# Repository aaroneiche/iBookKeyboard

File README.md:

# iBook Keyboard & Trackpad adapter

This board is a controller to drive a keyboard and trackpad on an Apple Clamshell iBook G3 - the original iBooks.

### Huh?

Yeah, I'm in the process of making an iBook chassis into a modern computer, and this is the first step. You can find more information (and progress) on this project at the [project page on my website](https://aaroneiche.com/projects/pibook).

### What are the JST connectors for?
Eventually I hope to integrate the controls for the Power button, trackpad button, and the lid-closed sensor (a magnetic *reed switch*). I haven't gotten to that yet, so for right now, they're just connectors that go to GPIO on the RP2040.

The RGB out is something where I'm hoping to support RGB LEDs to pass through the keyboard for fun. This is a "bells and whistles" type thing, and might not ever get addressed.

### Can I use it?
Yes, you can. But please be aware that I haven't finalized the design and I'm not sure that it'll work 100% yet. Also, the firmware is in an incomplete state (and not included in this repo yet), so *caveat emptor*. That said, if you have questions feel free to send me a message. I'm happy to help where I can.

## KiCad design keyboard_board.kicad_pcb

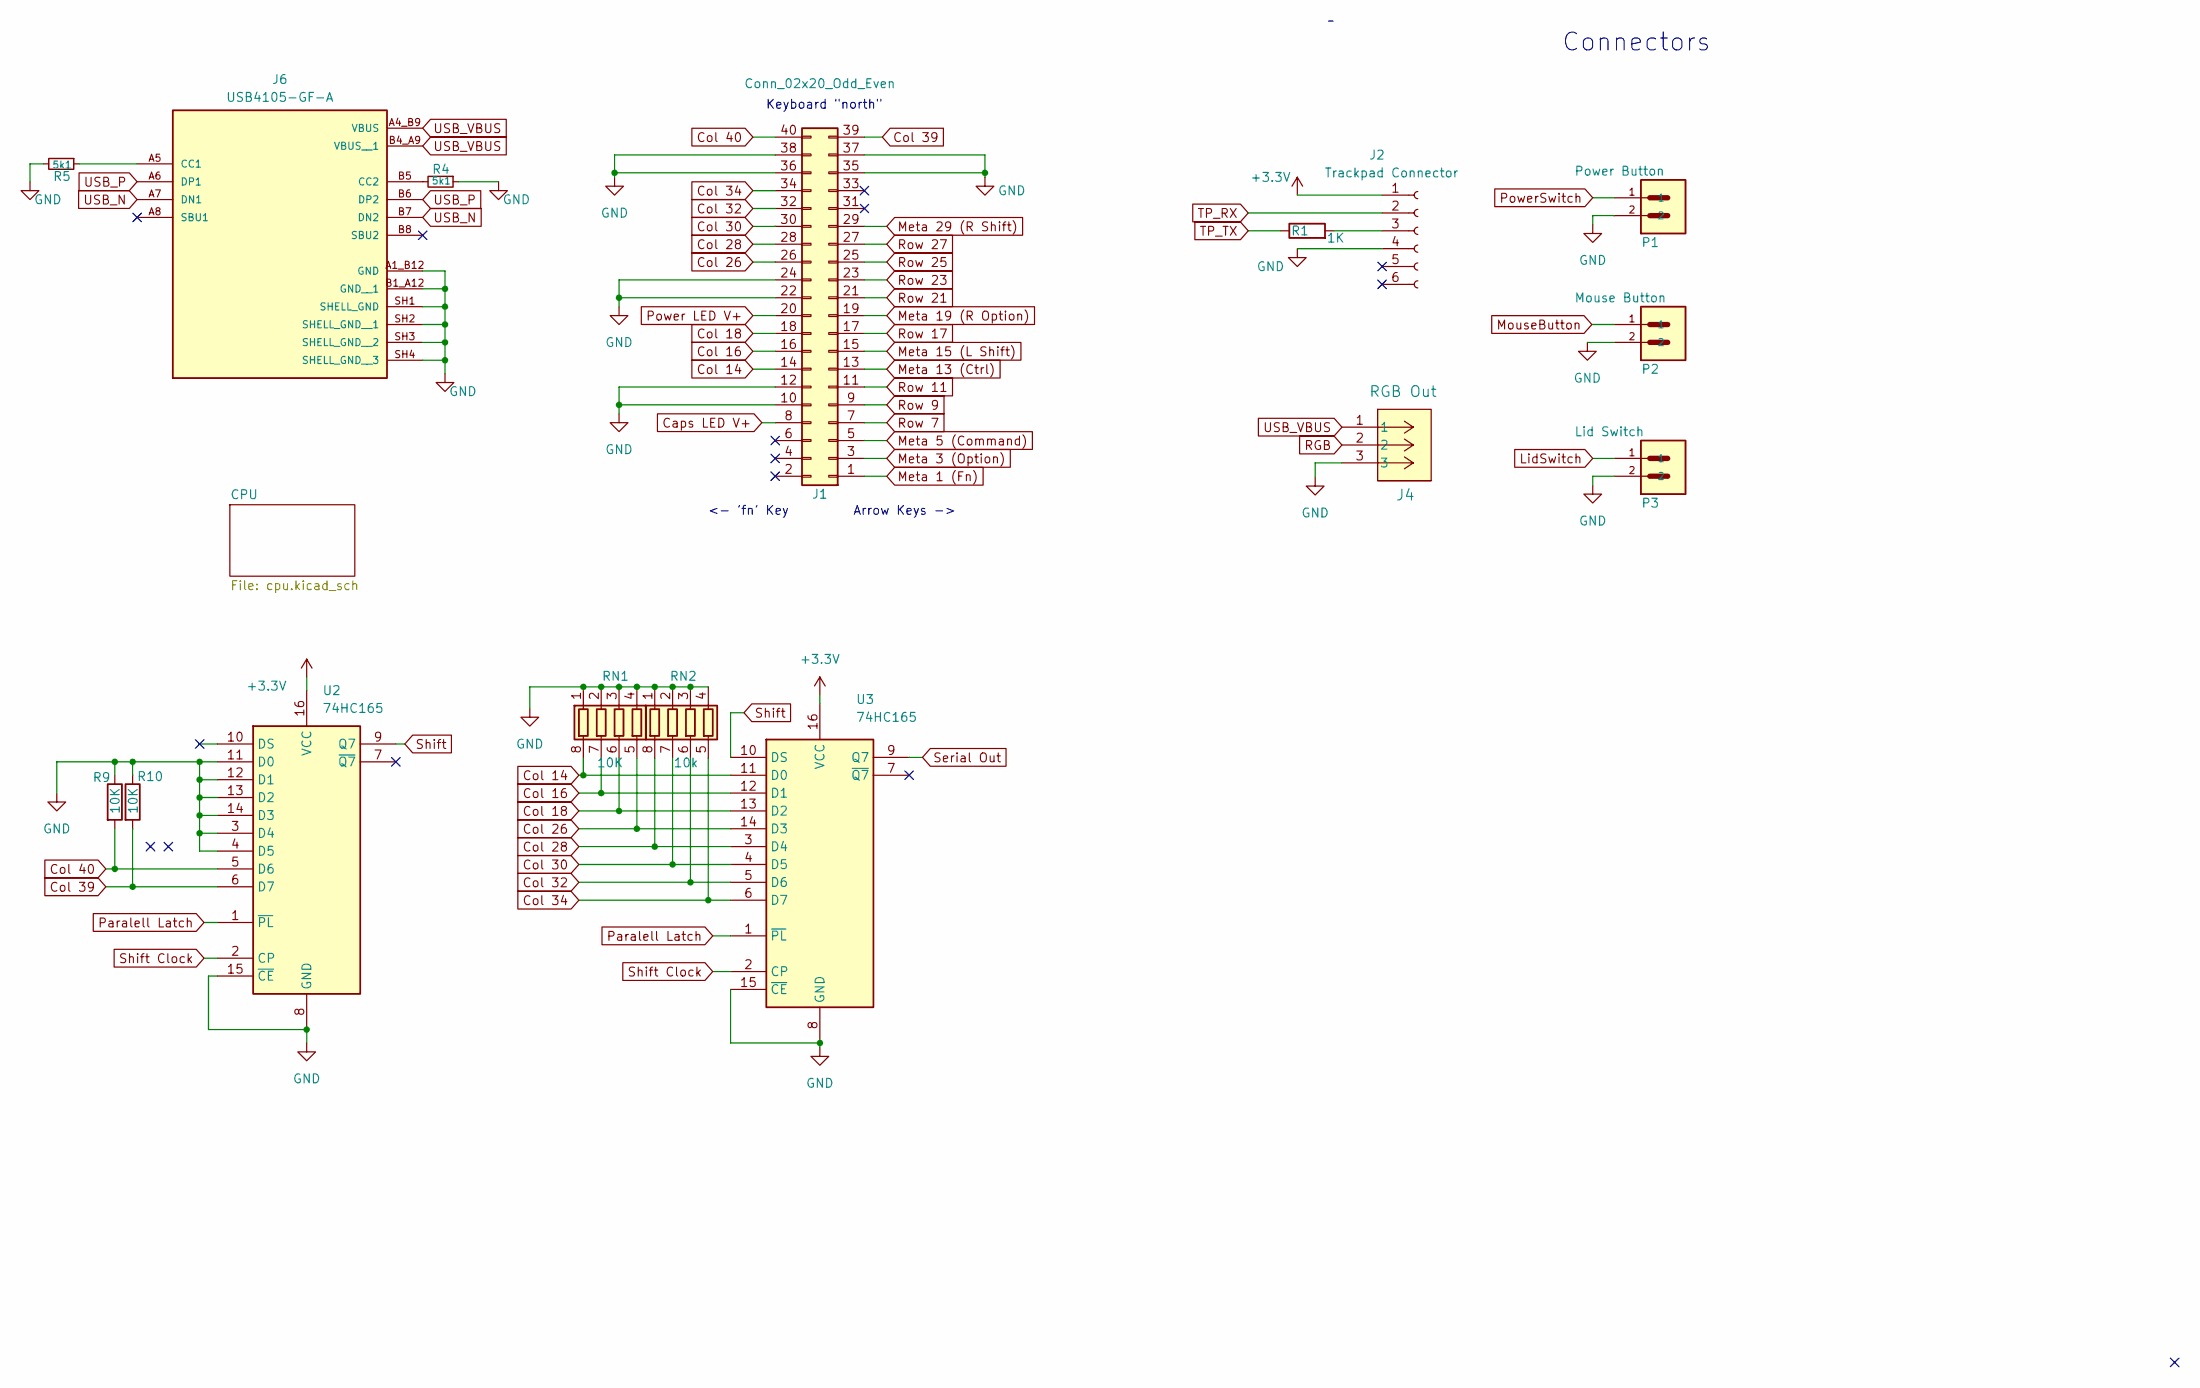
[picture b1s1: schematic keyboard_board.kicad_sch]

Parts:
J1: Conn_02x20_Odd_Even; 2x20_1.27_DIP_F
J2: Trackpad Connector; AMPHENOL_SFW6S-2STE1LF
J4: RGB Out; CONN3_S3B-PH_JST
J6: USB4105-GF-A; GCT_USB4105-GF-A; PARTREV B4
P1: Power Button; JST_S2B-PH-SM4-TB
P2: Mouse Button; JST_S2B-PH-SM4-TB
P3: Lid Switch; JST_S2B-PH-SM4-TB
R1: 1K; R_0805_2012Metric
R4, R5: 5k1; R_0603_1608Metric
R9, R10: 10K; R_0805_2012Metric
RN1: 10K; R_Array_Convex_4x1206
RN2: 10k; R_Array_Convex_4x1206
U2, U3: 74HC165; D16-L

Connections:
+3.3V: J2.1, U2.16 (VCC), U3.16 (VCC); also elsewhere on the board
Caps LED V+: J1.8; also elsewhere on the board
Col 14: J1.14, RN1.8 (R1.2), U3.11 (D0)
Col 16: J1.16, RN1.7 (R2.2), U3.12 (D1)
Col 18: J1.18, RN1.6 (R3.2), U3.13 (D2)
Col 26: J1.26, RN1.5 (R4.2), U3.14 (D3)
Col 28: J1.28, RN2.8 (R1.2), U3.3 (D4)
Col 30: J1.30, RN2.7 (R2.2), U3.4 (D5)
Col 32: J1.32, RN2.6 (R3.2), U3.5 (D6)
Col 34: J1.34, RN2.5 (R4.2), U3.6 (D7)
Col 39: J1.39, R10.2, U2.6 (D7)
Col 40: J1.40, R9.2, U2.5 (D6)
GND: J1.10, J1.12, J1.22, J1.24, J1.35, J1.36, J1.37, J1.38, J2.4, J4.3, J6.A1_B12 (GND), J6.B1_A12 (GND__1), J6.SH1 (SHELL_GND), J6.SH2 (SHELL_GND__1), J6.SH3 (SHELL_GND__2), J6.SH4 (SHELL_GND__3), P1.2, P2.2, P3.2, R4.1, R5.2, R9.1, R10.1, RN1.1 (R1.1), RN1.2 (R2.1), RN1.3 (R3.1), RN1.4 (R4.1), RN2.1 (R1.1), RN2.2 (R2.1), RN2.3 (R3.1), RN2.4 (R4.1), U2.3 (D4), U2.4 (D5), U2.8 (GND), U2.11 (D0), U2.12 (D1), U2.13 (D2), U2.14 (D3), U2.15 (~CE), U3.8 (GND), U3.15 (~CE); also elsewhere on the board
LidSwitch: P3.1; also elsewhere on the board
Meta 1 (Fn): J1.1; also elsewhere on the board
Meta 3 (Option): J1.3; also elsewhere on the board
Meta 5 (Command): J1.5; also elsewhere on the board
Meta 13 (Ctrl): J1.13; also elsewhere on the board
Meta 15 (L Shift): J1.15; also elsewhere on the board
Meta 19 (R Option): J1.19; also elsewhere on the board
Meta 29 (R Shift): J1.29; also elsewhere on the board
MouseButton: P2.1; also elsewhere on the board
unnamed: J2.3, R1.2
unnamed: J6.A5 (CC1), R5.1
unnamed: J6.B5 (CC2), R4.2
Paralell Latch: U2.1 (~PL), U3.1 (~PL); also elsewhere on the board
Power LED V+: J1.20; also elsewhere on the board
PowerSwitch: P1.1; also elsewhere on the board
RGB: J4.2; also elsewhere on the board
Row 7: J1.7; also elsewhere on the board
Row 9: J1.9; also elsewhere on the board
Row 11: J1.11; also elsewhere on the board
Row 17: J1.17; also elsewhere on the board
Row 21: J1.21; also elsewhere on the board
Row 23: J1.23; also elsewhere on the board
Row 25: J1.25; also elsewhere on the board
Row 27: J1.27; also elsewhere on the board
Serial Out: U3.9 (Q7); also elsewhere on the board
Shift: U2.9 (Q7), U3.10 (DS)
Shift Clock: U2.2 (CP), U3.2 (CP); also elsewhere on the board
TP_RX: J2.2; also elsewhere on the board
TP_TX: R1.1; also elsewhere on the board
USB_N: J6.A7 (DN1), J6.B7 (DN2); also elsewhere on the board
USB_P: J6.A6 (DP1), J6.B6 (DP2); also elsewhere on the board
USB_VBUS: J4.1, J6.A4_B9 (VBUS), J6.B4_A9 (VBUS__1); also elsewhere on the board

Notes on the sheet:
<- 'fn' Key
Connectors
Arrow Keys ->
Keyboard "north"

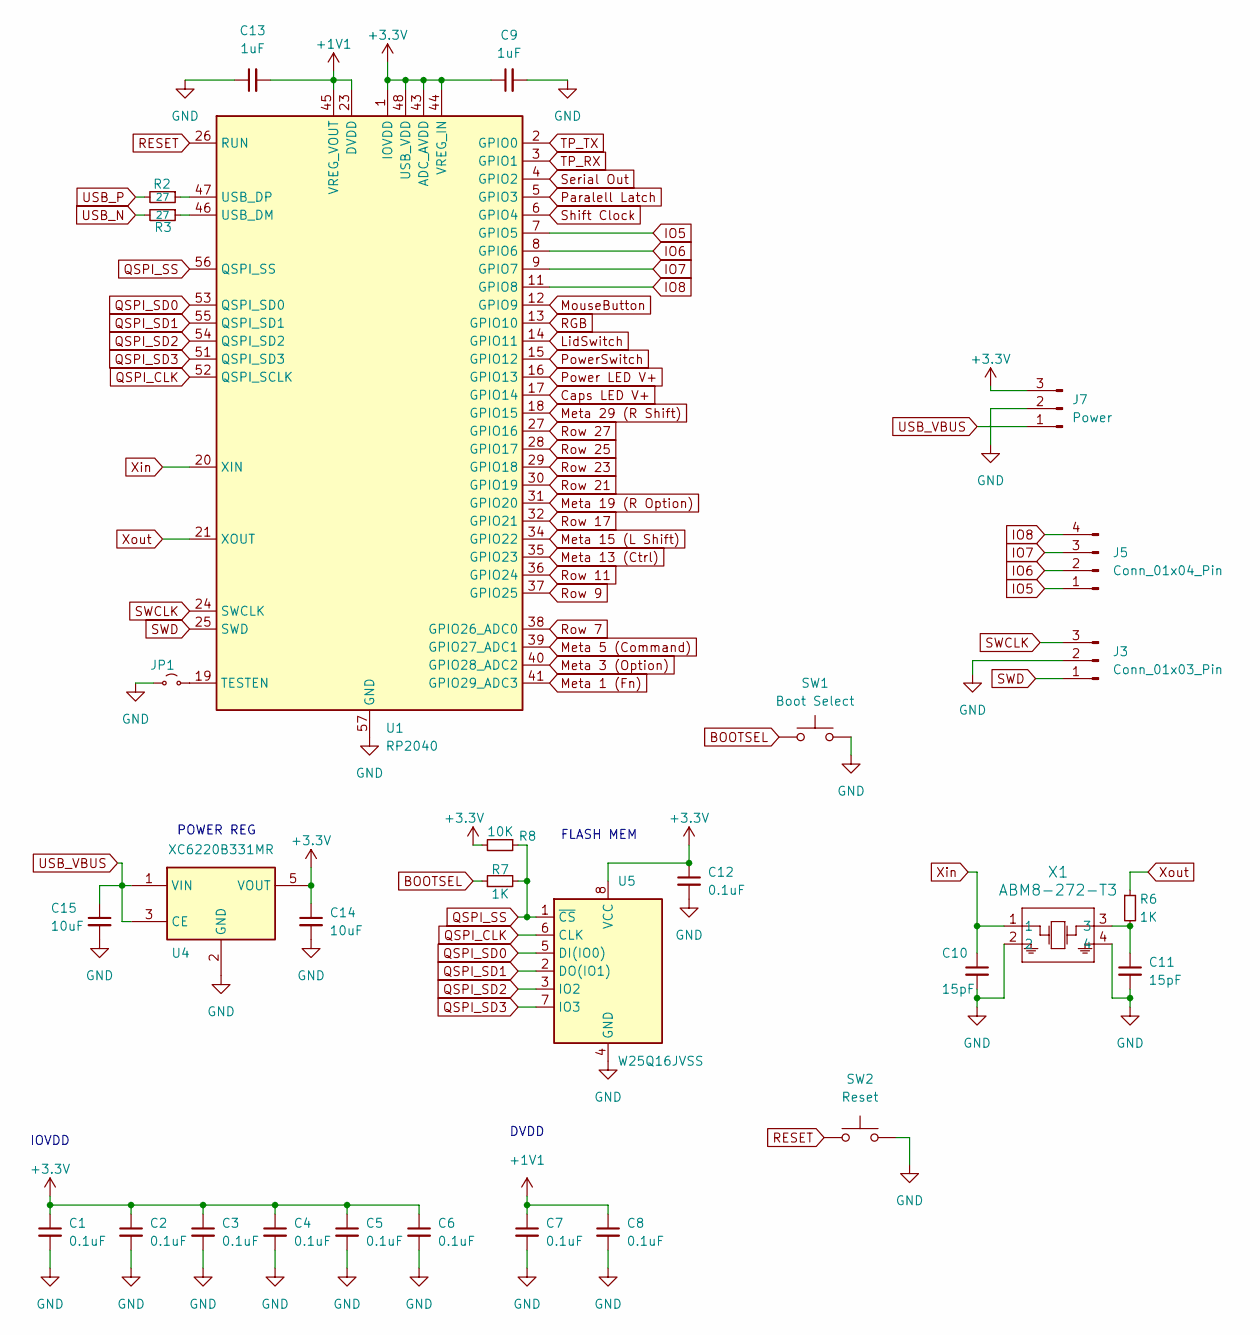
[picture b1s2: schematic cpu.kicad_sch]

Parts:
C1, C2, C3, C4, C5, C6, C7, C8, C12: 0.1uF; C_0603_1608Metric
C9, C13: 1uF; C_0603_1608Metric
C10, C11: 15pF; C_0603_1608Metric
C14, C15: 10uF; C_0805_2012Metric
J3: Conn_01x03_Pin; PinHeader_1x03_P2.54mm_Vertical
J5: Conn_01x04_Pin; PinHeader_1x04_P2.54mm_Vertical
J7: Power; PinHeader_1x03_P2.54mm_Vertical
JP1: Jumper_2_Small_Open; SolderJumper-2_P1.3mm_Open_RoundedPad1.0x1.5mm
R2, R3: 27; R_0603_1608Metric
R6, R7: 1K; R_0603_1608Metric
R8: 10K; R_0603_1608Metric
SW1: Boot Select; SW4_PTS815 SJM 250 SMTR LFS_CNK
SW2: Reset; SW4_PTS815 SJM 250 SMTR LFS_CNK
U1: RP2040; QFN-56-1EP_7x7mm_P0.4mm_EP3.2x3.2mm; Digikey P/N 2648-SC0914(13)CT-ND
U4: XC6220B331MR; SOT-23-5; Digikey P/N 296-50414-1-ND
U5: W25Q16JVSS; USON-8_UX_2x3x0p6_WIN; Digikey P/N 256-W25Q16JVUXIQTRCT-ND
X1: ABM8-272-T3; ABM8-272-T3_ABR

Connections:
+1V1: C7.1, C8.1, C13.2, U1.23 (DVDD), U1.45 (VREG_VOUT), U1.50 (DVDD)
+3.3V: C1.1, C2.1, C3.1, C4.1, C5.1, C6.1, C9.1, C12.1, C14.1, J7.3, R8.2, U1.1 (IOVDD), U1.10 (IOVDD), U1.22 (IOVDD), U1.33 (IOVDD), U1.42 (IOVDD), U1.43 (ADC_AVDD), U1.44 (VREG_IN), U1.48 (USB_VDD), U1.49 (IOVDD), U4.5 (VOUT), U5.8 (VCC); also elsewhere on the board
BOOTSEL: R7.1, SW1.1
Caps LED V+: U1.17 (GPIO14); also elsewhere on the board
GND: C1.2, C2.2, C3.2, C4.2, C5.2, C6.2, C7.2, C8.2, C9.2, C10.2, C11.2, C12.2, C13.1, C14.2, C15.2, J3.2, J7.2, JP1.1 (A), SW1.2, SW2.2, U1.57 (GND), U4.2 (GND), U5.4 (GND), X1.2, X1.4; also elsewhere on the board
IO5: J5.1, U1.7 (GPIO5)
IO6: J5.2, U1.8 (GPIO6)
IO7: J5.3, U1.9 (GPIO7)
IO8: J5.4, U1.11 (GPIO8)
LidSwitch: U1.14 (GPIO11); also elsewhere on the board
Meta 1 (Fn): U1.41 (GPIO29_ADC3); also elsewhere on the board
Meta 3 (Option): U1.40 (GPIO28_ADC2); also elsewhere on the board
Meta 5 (Command): U1.39 (GPIO27_ADC1); also elsewhere on the board
Meta 13 (Ctrl): U1.35 (GPIO23); also elsewhere on the board
Meta 15 (L Shift): U1.34 (GPIO22); also elsewhere on the board
Meta 19 (R Option): U1.31 (GPIO20); also elsewhere on the board
Meta 29 (R Shift): U1.18 (GPIO15); also elsewhere on the board
MouseButton: U1.12 (GPIO9); also elsewhere on the board
unnamed: C11.1, R6.2, X1.3
unnamed: JP1.2 (B), U1.19 (TESTEN)
unnamed: R3.1, U1.46 (USB_DM)
unnamed: R2.1, U1.47 (USB_DP)
Paralell Latch: U1.5 (GPIO3); also elsewhere on the board
Power LED V+: U1.16 (GPIO13); also elsewhere on the board
PowerSwitch: U1.15 (GPIO12); also elsewhere on the board
QSPI_CLK: U1.52 (QSPI_SCLK), U5.6 (CLK)
QSPI_SD0: U1.53 (QSPI_SD0), U5.5 (DI(IO0))
QSPI_SD1: U1.55 (QSPI_SD1), U5.2 (DO(IO1))
QSPI_SD2: U1.54 (QSPI_SD2), U5.3 (IO2)
QSPI_SD3: U1.51 (QSPI_SD3), U5.7 (IO3)
QSPI_SS: R7.2, R8.1, U1.56 (QSPI_SS), U5.1 (~CS)
RESET: SW2.1, U1.26 (RUN)
RGB: U1.13 (GPIO10); also elsewhere on the board
Row 7: U1.38 (GPIO26_ADC0); also elsewhere on the board
Row 9: U1.37 (GPIO25); also elsewhere on the board
Row 11: U1.36 (GPIO24); also elsewhere on the board
Row 17: U1.32 (GPIO21); also elsewhere on the board
Row 21: U1.30 (GPIO19); also elsewhere on the board
Row 23: U1.29 (GPIO18); also elsewhere on the board
Row 25: U1.28 (GPIO17); also elsewhere on the board
Row 27: U1.27 (GPIO16); also elsewhere on the board
SWCLK: J3.3, U1.24 (SWCLK)
SWD: J3.1, U1.25 (SWD)
Serial Out: U1.4 (GPIO2); also elsewhere on the board
Shift Clock: U1.6 (GPIO4); also elsewhere on the board
TP_RX: U1.3 (GPIO1); also elsewhere on the board
TP_TX: U1.2 (GPIO0); also elsewhere on the board
USB_N: R3.2; also elsewhere on the board
USB_P: R2.2; also elsewhere on the board
USB_VBUS: C15.1, J7.1, U4.1 (VIN), U4.3 (CE); also elsewhere on the board
Xin: C10.1, U1.20 (XIN), X1.1
Xout: R6.1, U1.21 (XOUT)

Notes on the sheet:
FLASH MEM
IOVDD
POWER REG
DVDD

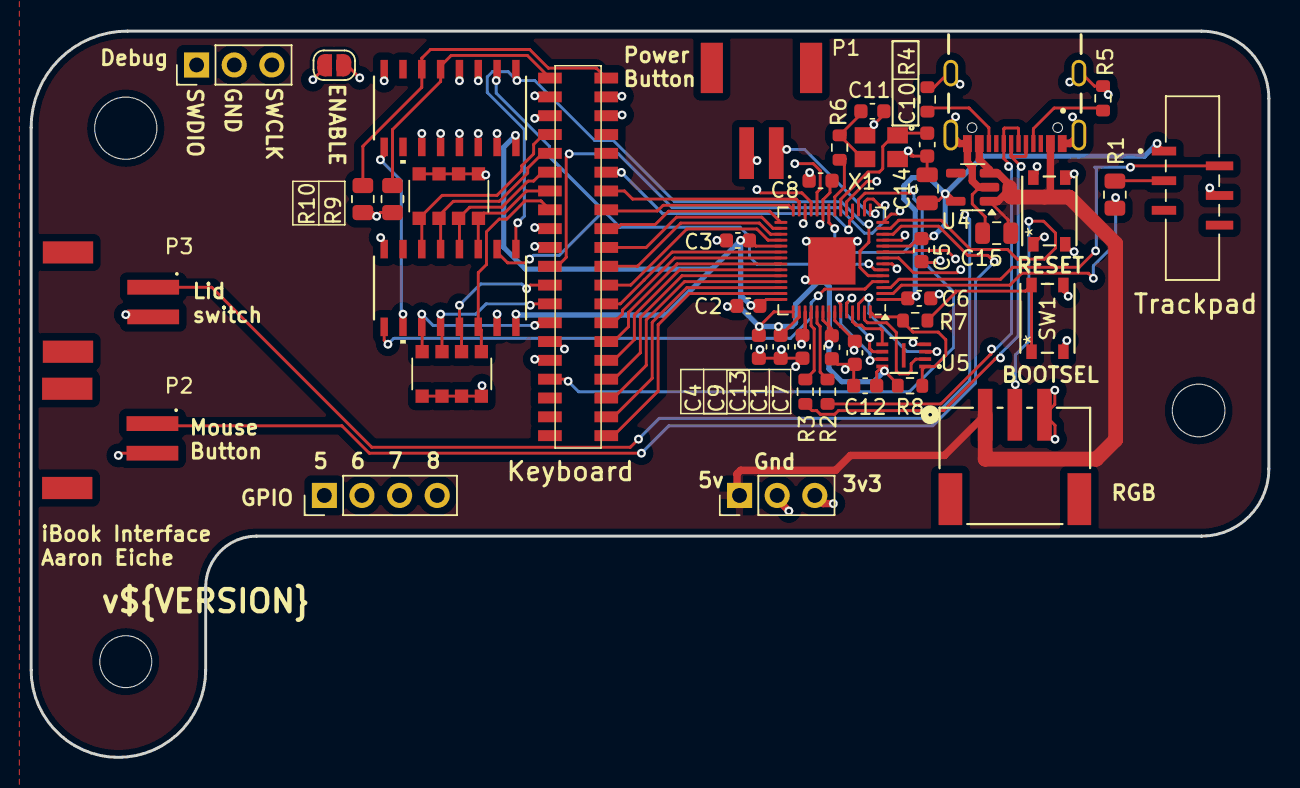
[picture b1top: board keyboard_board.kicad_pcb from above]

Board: 4 copper layers, 83.5 x 49.0 mm, 46 parts (0 on the bottom side), 66 nets.

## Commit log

2025-03-11 Initial commit - laid out board.
2025-03-12 -Changes USB labels to support differential pair - Does some major layout changes.
2025-03-13 Adds Power input 2-pin JST PH. Adds RGB output Adds Power Button input
2025-03-14 Adds Gerber files.
2025-03-19 Completes Pico version
2025-03-19 Updates to Pico version
2025-03-19 Updates to git ignore
2025-03-19 'gebers directory' removal
2025-03-21 Reworks Pico-based into discrete components
2025-05-12 prod version, I think
2025-05-12 adds sym-lib-table
2025-05-12 removing a zip file :p
2025-05-13 Adds a readme.
